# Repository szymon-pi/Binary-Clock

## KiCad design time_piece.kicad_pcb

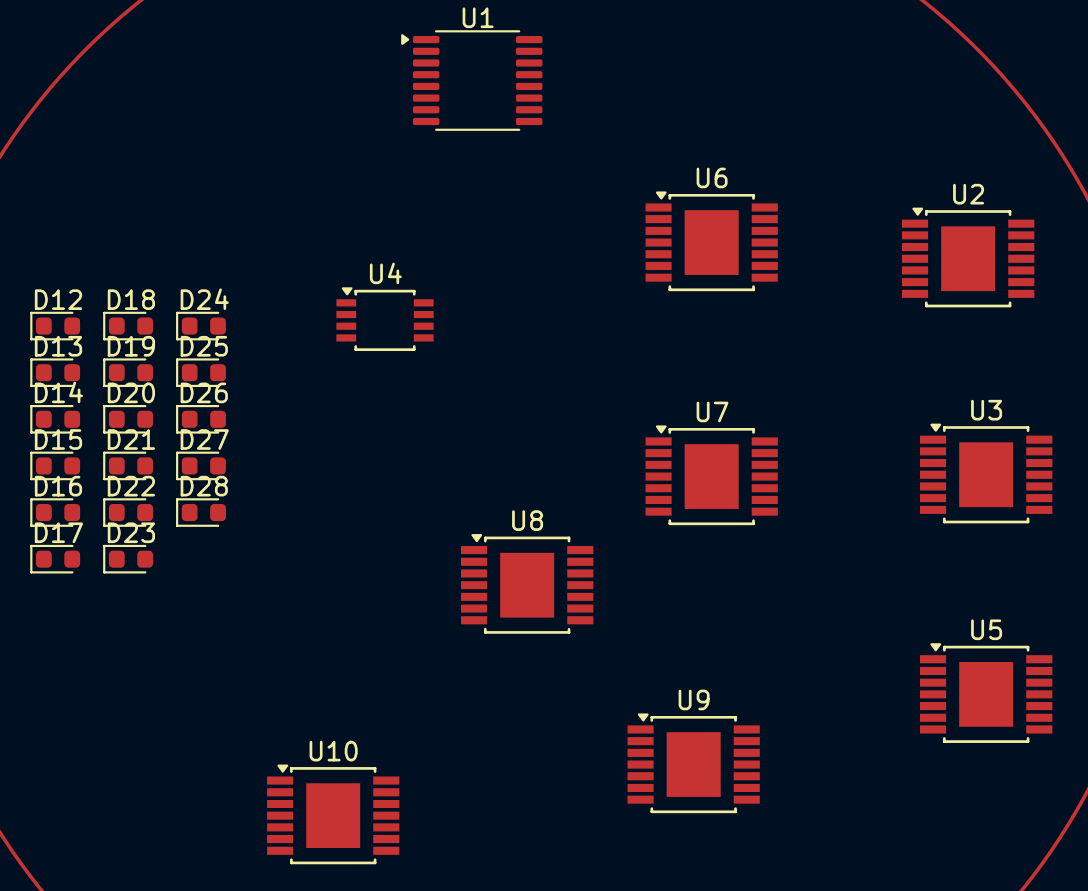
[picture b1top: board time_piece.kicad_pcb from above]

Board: 2 copper layers, 27 parts (0 on the bottom side), 30 nets, no tracks yet.

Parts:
D12, D13, D14, D15, D16, D17, D18, D19, D20, D21, D22, D23, D24, D25, D26, D27, D28: LED; LED_0603_1608Metric
U1: 74HC4060; TSSOP-16_4.4x5mm_P0.65mm
U2, U3, U9: 74HC393; TSSOP-14-1EP_4.4x5mm_P0.65mm
U4: 74AUP1G74; TSSOP-8_3x3mm_P0.65mm
U5: 74HC74; TSSOP-14-1EP_4.4x5mm_P0.65mm
U6, U7, U8, U10: 74HC00; TSSOP-14-1EP_4.4x5mm_P0.65mm

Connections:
+3.3V: U1.16 (VDD), U4.6 (~CLR), U4.7 (~PRE), U4.8 (VCC)
GND: U1.8 (VSS), U4.4 (GND)
unnamed: U8.4, U8.9, U10.9
unnamed: U1.12 (CLR), U4.5 (Q)
unnamed: U1.3 (Q14), U2.1 (CP), U8.6
unnamed: U2.2 (MR), U2.12 (MR), U3.1 (CP), U6.6, U8.8
unnamed: U2.5 (Q2), U6.1
unnamed: U2.6 (Q3), U2.13 (CP), U6.2
unnamed: U2.11 (Q0), U6.9
unnamed: U2.10 (Q1), U6.10
unnamed: U3.2 (MR), U3.12 (MR), U7.6, U9.1 (CP), U10.8
unnamed: U3.5 (Q2), U6.12
unnamed: U3.6 (Q3), U3.13 (CP), U6.13
unnamed: U3.11 (Q0), U7.1
unnamed: U3.10 (Q1), U7.2
unnamed: U4.2 (D), U4.3 (~Q)
unnamed: U5.2 (D), U5.6 (~Q), U5.11 (C), U7.9
unnamed: U5.5 (Q), U8.1, U8.12
unnamed: U5.8 (~Q), U5.12 (D), U8.2
unnamed: U5.9 (Q), U7.10, U8.13
unnamed: U6.3, U6.4
unnamed: U6.5, U6.8
unnamed: U6.11, U7.4
unnamed: U7.3, U7.5
unnamed: U7.8, U8.10
unnamed: U8.3, U8.5
unnamed: U7.11, U9.2 (MR), U9.12 (MR)
unnamed: U7.12, U9.6 (Q3), U9.13 (CP)
unnamed: U7.13, U9.11 (Q0)
unnamed: U8.11, U10.10
